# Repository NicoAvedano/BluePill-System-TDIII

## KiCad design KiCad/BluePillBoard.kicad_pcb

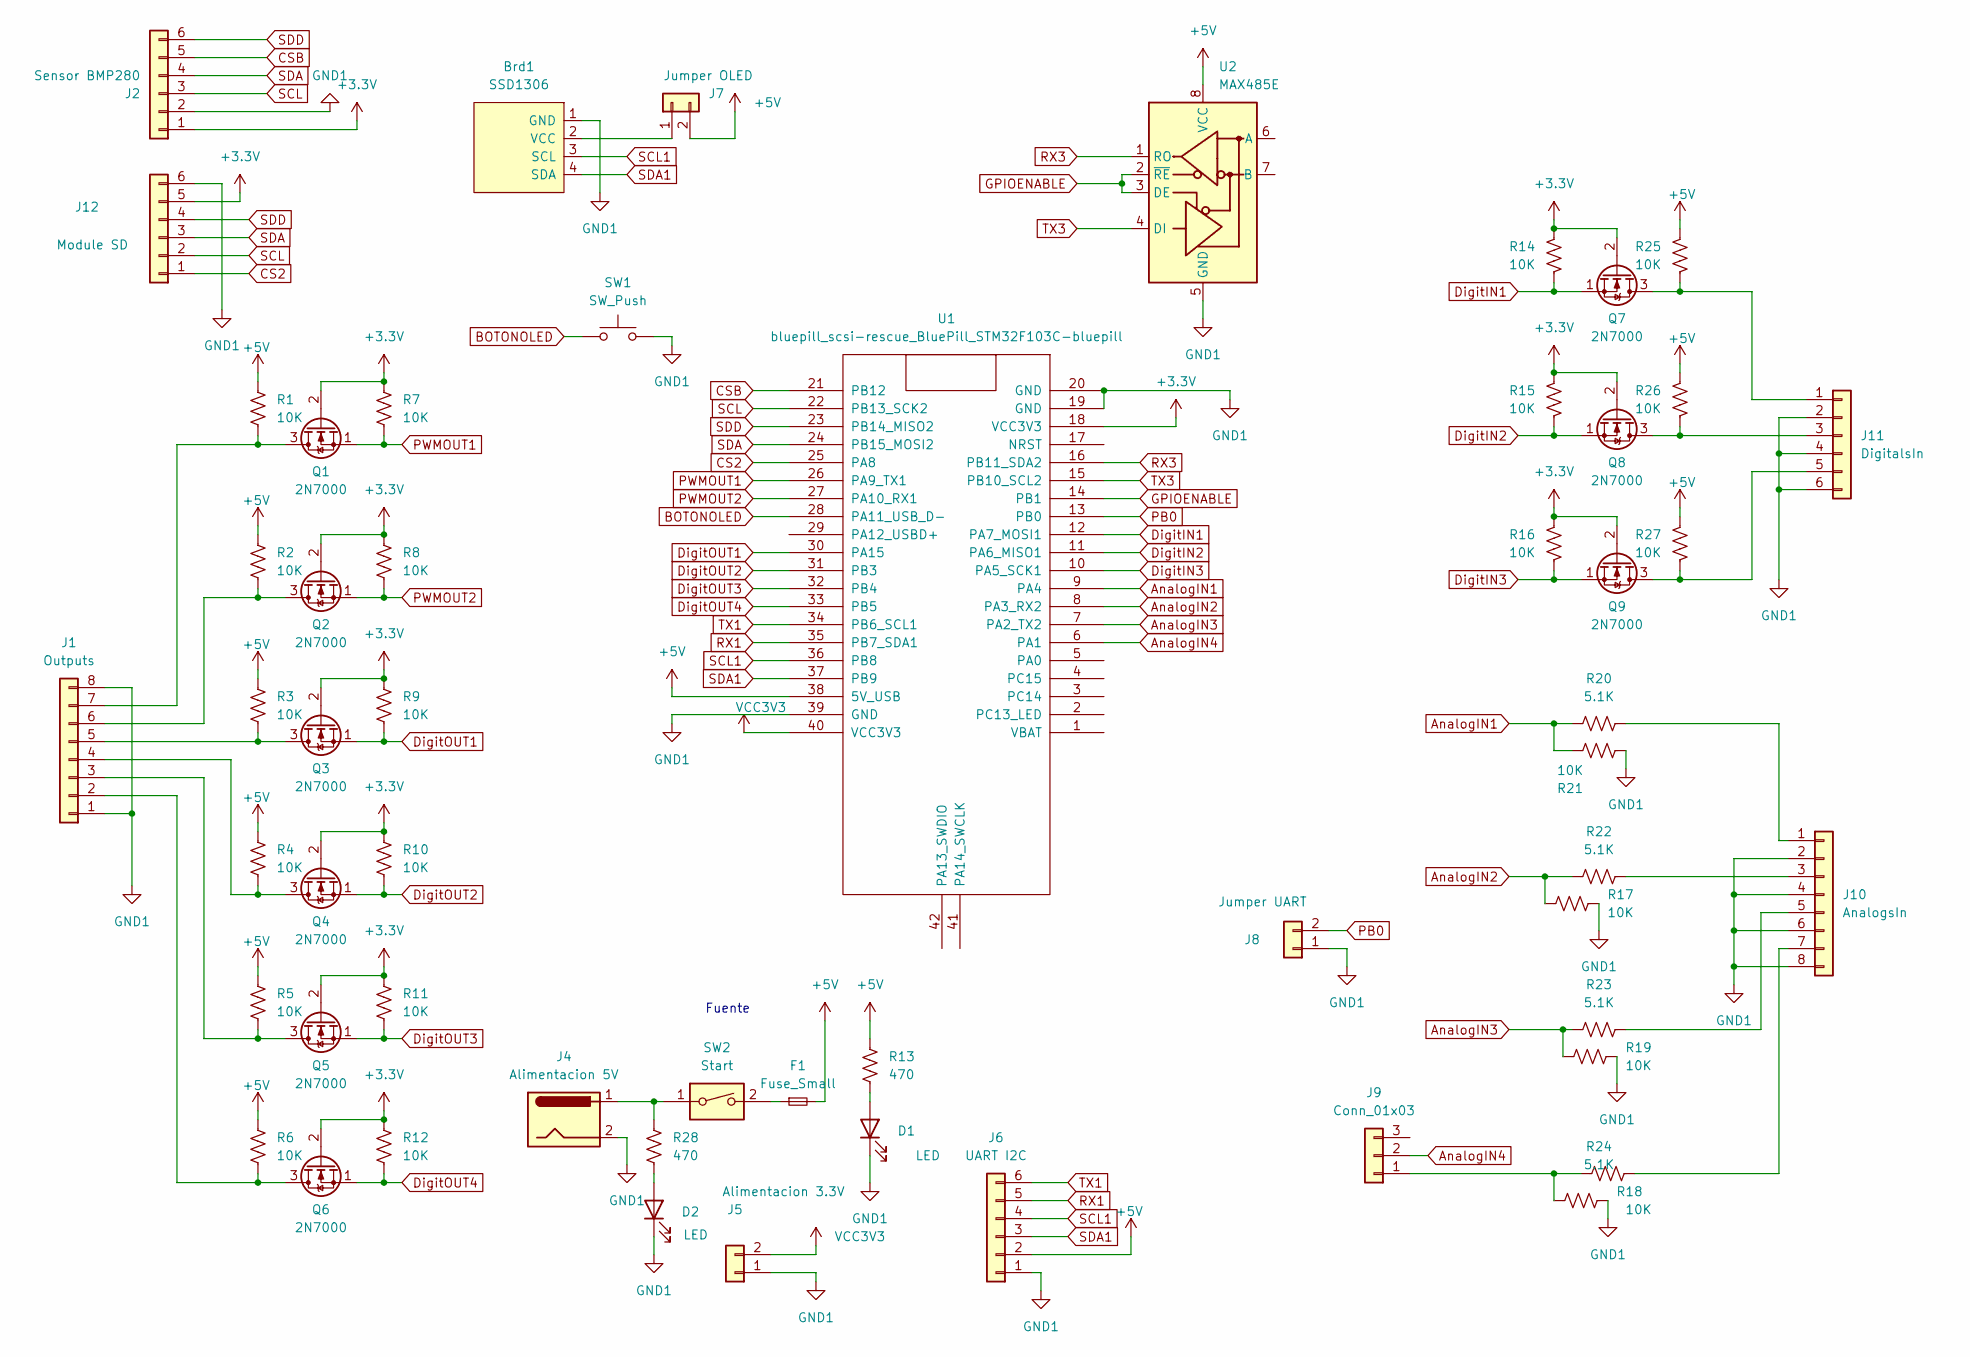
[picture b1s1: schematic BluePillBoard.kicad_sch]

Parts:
Brd1: SSD1306; 128x64OLED
D1, D2: LED; LED_D3.0mm
F1: Fuse_Small; Fuseholder_Clip-5x20mm_Schurter_OG_Lateral_P15.00x5.00mm_D1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
J1: Outputs; PinSocket_1x08_P2.54mm_Vertical
J2: Sensor BMP280; PinSocket_1x06_P2.54mm_Vertical
J4: Alimentacion 5V; BarrelJack_Horizontal
J5: Alimentacion 3.3V; PinSocket_1x02_P2.54mm_Vertical
J6: UART I2C; PinSocket_1x06_P2.54mm_Vertical
J7: Jumper OLED; PinHeader_1x02_P2.54mm_Vertical
J8: Jumper UART; PinHeader_1x02_P2.54mm_Vertical
J9: Conn_01x03; PinHeader_1x03_P2.54mm_Vertical
J10: AnalogsIn; TerminalBlock_Phoenix_MKDS-1,5-8-5.08_1x08_P5.08mm_Horizont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
J11: DigitalsIn; PinSocket_1x06_P2.54mm_Vertical
J12: Module SD; PinSocket_1x06_P2.54mm_Vertical
Q1, Q2, Q3, Q4, Q5, Q6, Q7, Q8, Q9: 2N7000; TO-92L_Inline_Wide
R1, R2, R7, R8, R9, R10, R11, R12, R14, R15, R16, R17, R18, R19, R21, R25: 10K; R_Axial_DIN0207_L6.3mm_D2.5mm_P5.08mm_Vertical
R3, R4, R5, R6, R26, R27: 10K; R_Axial_DIN0207_L6.3mm_D2.5mm_P10.16mm_Horizontal
R13, R28: 470; R_Axial_DIN0207_L6.3mm_D2.5mm_P2.54mm_Vertical
R20, R22, R23, R24: 5.1K; R_Axial_DIN0207_L6.3mm_D2.5mm_P5.08mm_Vertical
SW1: SW_Push; SW_PUSH_6mm_H5mm
SW2: Start; SW_DIP_SPSTx01_Slide_9.78x4.72mm_W7.62mm_P2.54mm
U1: bluepill_scsi-rescue_BluePill_STM32F103C-bluepill; BluePill_STM32F103C
U2: MAX485E; TerminalBlock_Phoenix_PTSM-0,5-4-2.5-H-THR_1x04_P2.50mm_Hor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

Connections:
+3.3V: J2.1, J12.5, Q1.2 (G), Q2.2 (G), Q3.2 (G), Q4.2 (G), Q5.2 (G), Q6.2 (G), Q7.2 (G), Q8.2 (G), Q9.2 (G), R7.2, R8.2, R9.2, R10.2, R11.2, R12.2, R14.2, R15.2, R16.2, U1.18 (VCC3V3)
+5V: F1.2, J6.2, J7.2, R1.2, R2.2, R3.2, R4.2, R5.2, R6.2, R13.1, R25.2, R26.2, R27.2, U1.38 (5V_USB), U2.8 (VCC)
AnalogIN1: R20.1, R21.2, U1.9 (PA4)
AnalogIN2: R17.1, R22.1, U1.8 (PA3_RX2)
AnalogIN3: R19.1, R23.1, U1.7 (PA2_TX2)
AnalogIN4: J9.2, U1.6 (PA1)
BOTONOLED: SW1.1, U1.28 (PA11_USB_D-)
CS2: J12.1, U1.25 (PA8)
CSB: J2.5, U1.21 (PB12)
DigitIN1: Q7.1 (S), R14.1, U1.12 (PA7_MOSI1)
DigitIN2: Q8.1 (S), R15.1, U1.11 (PA6_MISO1)
DigitIN3: Q9.1 (S), R16.1, U1.10 (PA5_SCK1)
DigitOUT1: Q3.1 (S), R9.1, U1.30 (PA15)
DigitOUT2: Q4.1 (S), R10.1, U1.31 (PB3)
DigitOUT3: Q5.1 (S), R11.1, U1.32 (PB4)
DigitOUT4: Q6.1 (S), R12.1, U1.33 (PB5)
GND1: Brd1.1 (GND), D1.1 (K), D2.1 (K), J1.1, J1.8, J2.2, J4.2, J5.1, J6.1, J8.1, J10.2, J10.4, J10.6, J10.8, J11.2, J11.4, J11.6, J12.6, R17.2, R18.2, R19.2, R21.1, SW1.2, U1.19 (GND), U1.20 (GND), U1.39 (GND), U2.5 (GND)
GPIOENABLE: U1.14 (PB1), U2.2 (~RE), U2.3 (DE)
unnamed: Brd1.2 (VCC), J7.1
unnamed: D1.2 (A), R13.2
unnamed: D2.2 (A), R28.2
unnamed: F1.1, SW2.2
unnamed: J1.2, Q6.3 (D), R6.1
unnamed: J1.3, Q5.3 (D), R5.1
unnamed: J1.4, Q4.3 (D), R4.1
unnamed: J1.5, Q3.3 (D), R3.1
unnamed: J1.6, Q2.3 (D), R2.1
unnamed: J1.7, Q1.3 (D), R1.1
unnamed: J4.1, R28.1, SW2.1
unnamed: J9.1, R18.1, R24.1
unnamed: J10.1, R20.2
unnamed: J10.3, R22.2
unnamed: J10.5, R23.2
unnamed: J10.7, R24.2
unnamed: J11.1, Q7.3 (D), R25.1
unnamed: J11.3, Q8.3 (D), R26.1
unnamed: J11.5, Q9.3 (D), R27.1
PB0: J8.2, U1.13 (PB0)
PWMOUT1: Q1.1 (S), R7.1, U1.26 (PA9_TX1)
PWMOUT2: Q2.1 (S), R8.1, U1.27 (PA10_RX1)
RX1: J6.5, U1.35 (PB7_SDA1)
RX3: U1.16 (PB11_SDA2), U2.1 (RO)
SCL: J2.3, J12.2, U1.22 (PB13_SCK2)
SCL1: Brd1.3 (SCL), J6.4, U1.36 (PB8)
SDA: J2.4, J12.3, U1.24 (PB15_MOSI2)
SDA1: Brd1.4 (SDA), J6.3, U1.37 (PB9)
SDD: J2.6, J12.4, U1.23 (PB14_MISO2)
TX1: J6.6, U1.34 (PB6_SCL1)
TX3: U1.15 (PB10_SCL2), U2.4 (DI)
VCC3V3: J5.2, U1.40 (VCC3V3)

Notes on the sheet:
Fuente

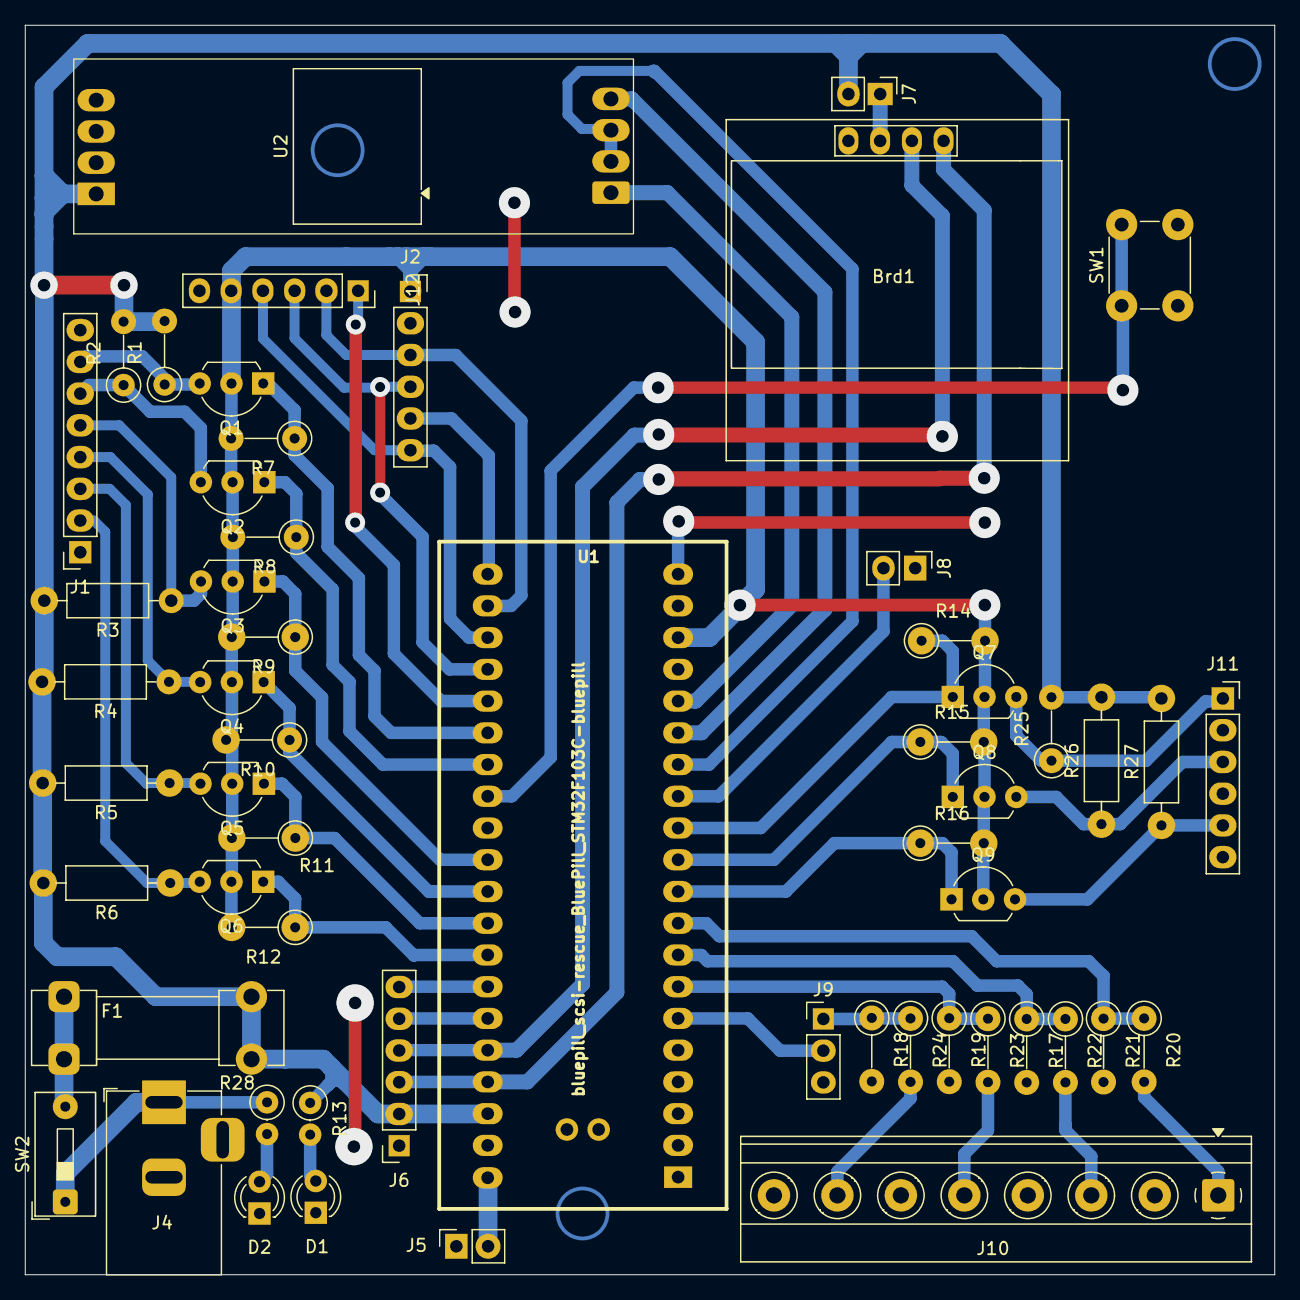
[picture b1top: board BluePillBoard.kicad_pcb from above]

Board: 2 copper layers, 100.0 x 100.0 mm, 56 parts (0 on the bottom side), 50 nets.

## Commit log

2025-06-05 Create a
